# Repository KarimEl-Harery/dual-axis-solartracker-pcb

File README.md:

# Dual Axis Solar Tracker PCB

This repository contains the **PCB design and electronics for a mobile IoT-monitored dual-axis solar tracking system**.

The system automatically aligns a photovoltaic panel with the position of the sun to maximize solar energy generation.

The project combines **mechanical design, embedded systems, PCB development, and IoT communication**.

---

# 📄 Paper

The full project description is available in the paper:

➡️ **[Read the Paper](EMS-Gruppe%2016_STRZYZEWSKI_GAJIC_EL-Harery.pdf)**

---

# 🛰 Solar Tracker System

The system uses an **Arduino Uno WiFi Rev2** to calculate the sun position based on GPS data and automatically align the photovoltaic panel using two motorized axes:

- **Azimuth rotation**
- **Altitude rotation**

The tracker communicates with an **IoT platform via WiFi using MQTT**.

---

# 🔌 PCB Design

The project includes a custom **Arduino Shield PCB** which integrates:

- Stepper motor control
- Sensor interfaces (light, temperature, GPS)
- Power management
- Communication interfaces

---

# ⚙️ System Architecture

The solar tracker consists of three main subsystems:

### Embedded Control

- Arduino Uno WiFi Rev2
- Sun position calculation via library
- Stepper motor control
- Sensor data acquisition

### Electronics

Custom PCB providing:

- Motor driver interfaces
- Sensor connections
- GPS interface
- Power distribution

### Mechanical System

- **3D printed planetary gearbox** for altitude motion
- **Worm gear transmission** for azimuth motion
- Mobile solar platform

---

# 🌐 IoT Monitoring

System data is transmitted to an IoT platform via **WiFi using MQTT**.

Monitored parameters include:

- GPS position
- Solar panel orientation
- Illumination data
- Temperature
- System status

---

# 🔋 Power System

The system is powered by a **3S Li-Po battery (11.1V)** which is charged by the photovoltaic panel.

---

# 👨‍🔬 Authors  
Karim El-Harery

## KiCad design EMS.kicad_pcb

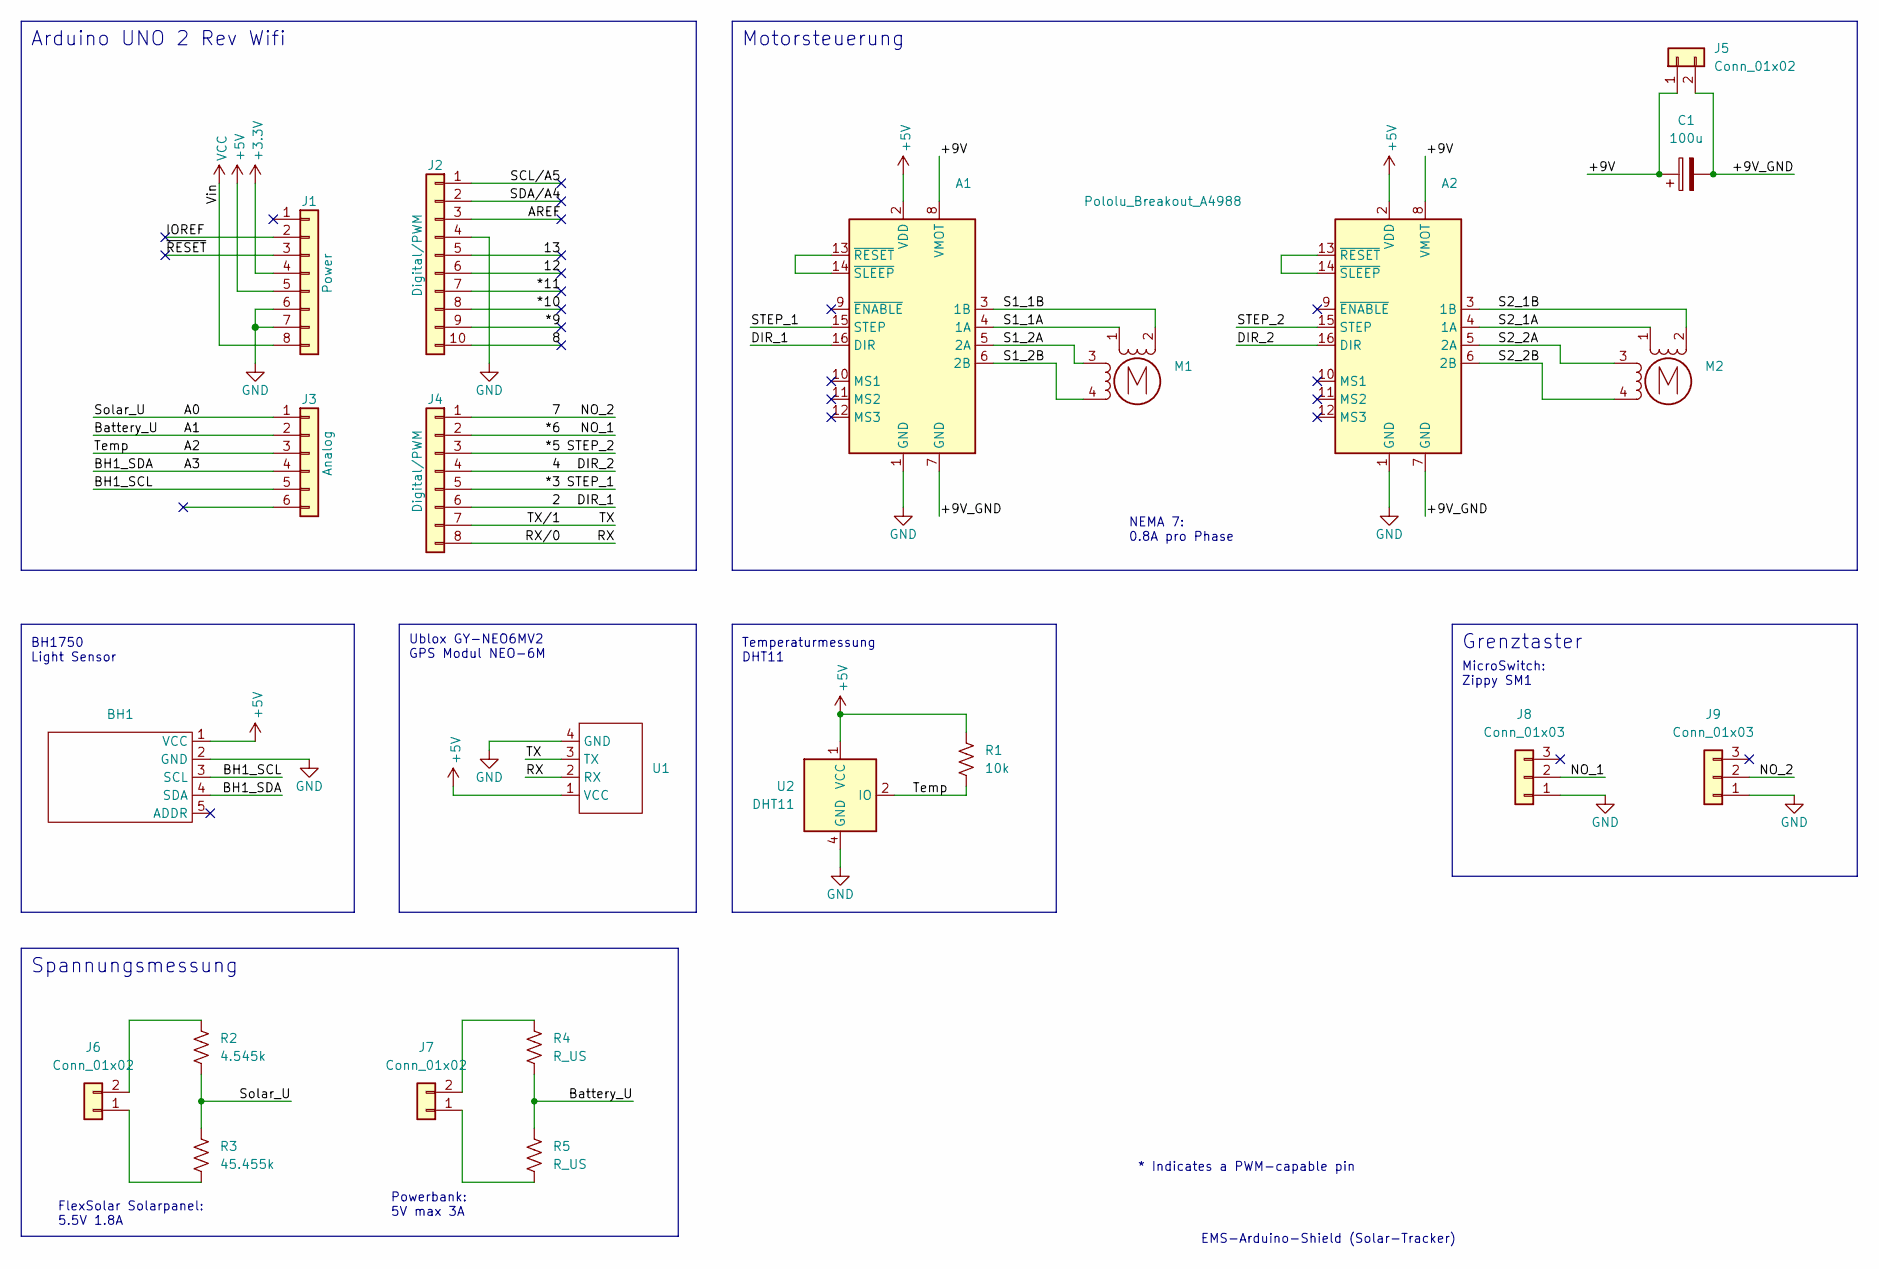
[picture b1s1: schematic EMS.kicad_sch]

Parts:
A1, A2: Pololu_Breakout_A4988; Pololu_Breakout-16_15.2x20.3mm
BH1: JST_XH_B5B-XH-A_1x05_P2.50mm_Vertical
C1: 100u; CP_Radial_D5.0mm_P2.50mm
J1: Power; PinSocket_1x08_P2.54mm_Vertical
J2: Digital/PWM; PinSocket_1x10_P2.54mm_Vertical
J3: Analog; PinSocket_1x06_P2.54mm_Vertical
J4: Digital/PWM; PinSocket_1x08_P2.54mm_Vertical
J5, J6, J7: Conn_01x02; JST_XH_B2B-XH-A_1x02_P2.50mm_Vertical
J8, J9: Conn_01x03; JST_XH_B2B-XH-A_1x02_P2.50mm_Vertical
M1, M2: Stepper_Motor_bipolar; JST_XH_B4B-XH-A_1x04_P2.50mm_Vertical
R1: 10k; R_Axial_DIN0207_L6.3mm_D2.5mm_P7.62mm_Horizontal
R2: 4.545k; R_Axial_DIN0207_L6.3mm_D2.5mm_P7.62mm_Horizontal
R3: 45.455k; R_Axial_DIN0207_L6.3mm_D2.5mm_P7.62mm_Horizontal
R4, R5: R_US; R_Axial_DIN0207_L6.3mm_D2.5mm_P7.62mm_Horizontal
U1: PinSocket_1x04_P2.54mm_Vertical
U2: DHT11; Aosong_DHT11_5.5x12.0_P2.54mm

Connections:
+3V3: J1.4
+5V: A1.2 (VDD), A2.2 (VDD), BH1.1 (VCC), J1.5, R1.1, U1.1 (VCC), U2.1 (VCC)
/2: A1.16 (DIR), J4.6
/4: A2.16 (DIR), J4.4
/7: J4.1, J9.2
/8: J2.10
/12: J2.6
/13: J2.5
/*3: A1.15 (STEP), J4.5
/*5: A2.15 (STEP), J4.3
/*6: J4.2, J8.2
/*9: J2.9
/*10: J2.8
/*11: J2.7
/+9V: A1.8 (VMOT), A2.8 (VMOT), C1.1, J5.1
/+9V_GND: A1.7 (GND), A2.7 (GND), C1.2, J5.2
/A0: J3.1, R2.2, R3.1
/A1: J3.2, R4.2, R5.1
/A2: J3.3, R1.2, U2.2 (IO)
/A3: BH1.4 (SDA), J3.4
/AREF: J2.3
/BH1_SCL: BH1.3 (SCL), J3.5
/IOREF: J1.2
/RX: J4.8, U1.2 (RX)
/S1_1A: A1.4 (1A), M1.1
/S1_1B: A1.3 (1B), M1.2 (-)
/S1_2A: A1.5 (2A), M1.3
/S1_2B: A1.6 (2B), M1.4
/S2_1A: A2.4 (1A), M2.1
/S2_1B: A2.3 (1B), M2.2 (-)
/S2_2A: A2.5 (2A), M2.3
/S2_2B: A2.6 (2B), M2.4
/SCL/A5: J2.1
/SDA/A4: J2.2
/TX: J4.7, U1.3 (TX)
/~RESET: J1.3
GND: A1.1 (GND), A2.1 (GND), BH1.2 (GND), J1.6, J1.7, J2.4, J8.1, J9.1, U1.4 (GND), U2.4 (GND)
unnamed: A1.13 (~RESET), A1.14 (~SLEEP)
unnamed: A2.13 (~RESET), A2.14 (~SLEEP)
unnamed: J6.1, R3.2
unnamed: J6.2, R2.1
unnamed: J7.1, R5.2
unnamed: J7.2, R4.1
VCC: J1.8

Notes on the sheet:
BH1750 Light Sensor
Temperaturmessung DHT11
EMS-Arduino-Shield (Solar-Tracker)
MicroSwitch: Zippy SM1
Spannungsmessung
FlexSolar Solarpanel: 5.5V 1.8A
Ublox GY-NEO6MV2 GPS Modul NEO-6M
NEMA 7: 0.8A pro Phase
Powerbank: 5V max 3A
Motorsteuerung
Arduino UNO 2 Rev Wifi
* Indicates a PWM-capable pin
Grenztaster

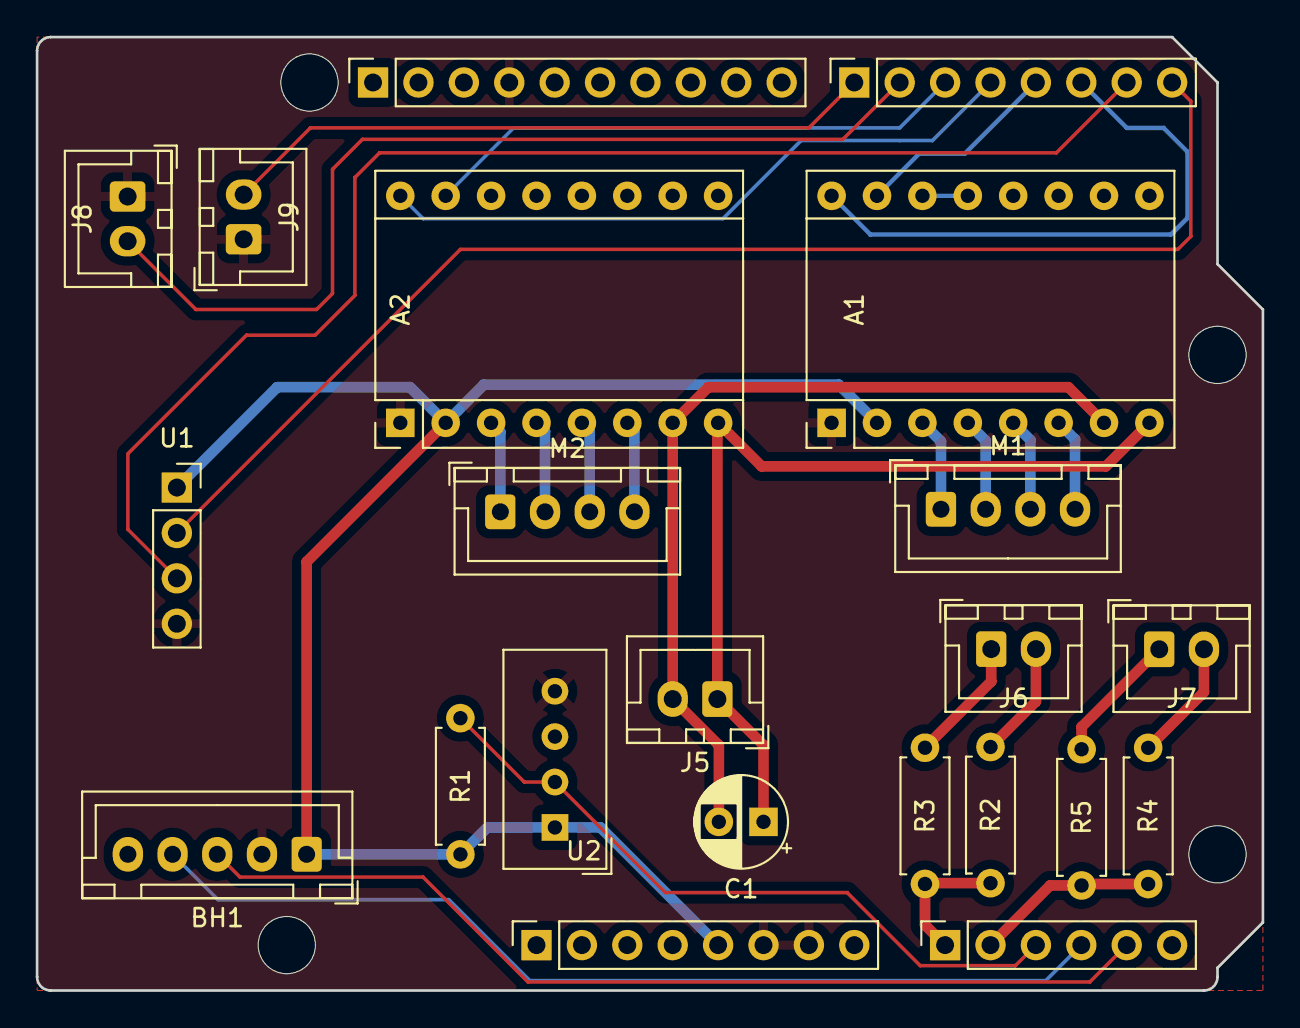
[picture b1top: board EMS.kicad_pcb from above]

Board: 2 copper layers, 68.6 x 53.3 mm, 26 parts (0 on the bottom side), 31 nets.

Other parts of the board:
MH1, MH2, MH3, MH4: MountingHole_3.2mm
